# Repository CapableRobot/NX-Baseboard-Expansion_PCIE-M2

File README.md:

# NX Baseboard Expansion : PCIe m2 E-Key

This repository holds the open-source files for the PCIe m2 E-Key add-on to the NX Baseboard.  The [NX Baseboard](https://github.com/antmicro/jetson-nano-baseboard) is also open-source, is designed by Antmicro, and is [sold by Capable Robot Components](https://capablerobot.com/products/nx-baseboard/).

Assembled and tested PCBAs are available for purchase on the [Capable Robot website](https://capablerobot.com/products/nx-baseboard/).

The NX PCIe m.2 E Key PCB provides a standard interface to the NVIDIA NX's PCIe x1 bus, which is exposed on the NX Baseboard via a 10-pin FFC connector. Board specifications:

- m.2 E-Key (PCIe + USB), 2230 size. This is commonly used for WIFI modules like the Intel 8265.
- PCIe x1 interface and 3.3v power are connected to the Host via a 10-pin 0.5mm flex cable.
- USB interface exposed via micro-USB port, allowing USB-specific functionality of the installed card (like Bluetooth) to be used if cabled to the Host. With USB connected, a local 5v to 3.3v regulator can be used in lieu of the 3.3v input on the FFC connector.

Hole spacing on the PCB and location of the flex connector matches that of the NX Baseboard, allowing it to be assembled onto the bottom of the Baseboard.

Any WIFI module that supports m.2 E Key 2230 size can be used with the PCB. We recommend (and stock) the Intel 8265 due to built-in support within NVIDIA Jetpack BSPs.

## License Information

| **Type** | **License** |
| --- | --- |
| Hardware | Copyright Capable Robot Components 2020 <br><br>This source describes Open Hardware and is licensed under the [CERN-OHL-P v2](https://ohwr.org/cern_ohl_p_v2.txt). <br/><br/> You may redistribute and modify this documentation and make products using it under the terms of the [CERN-OHL-P v2](https:/cern.ch/cern-ohl). This documentation is distributed WITHOUT ANY EXPRESS OR IMPLIED WARRANTY, INCLUDING OF MERCHANTABILITY, SATISFACTORY QUALITY AND FITNESS FOR A PARTICULAR PURPOSE. Please see the CERN-OHL-P v2 for applicable conditions |
| Software | NA |
| Documentation | [Creative Commons Attribution-ShareAlike](https://creativecommons.org/licenses/by-sa/4.0/) License |

More detailed information about the CERN License is available in the [license](license) folder and on the [CERN website](https://ohwr.org/project/cernohl/wikis/home).

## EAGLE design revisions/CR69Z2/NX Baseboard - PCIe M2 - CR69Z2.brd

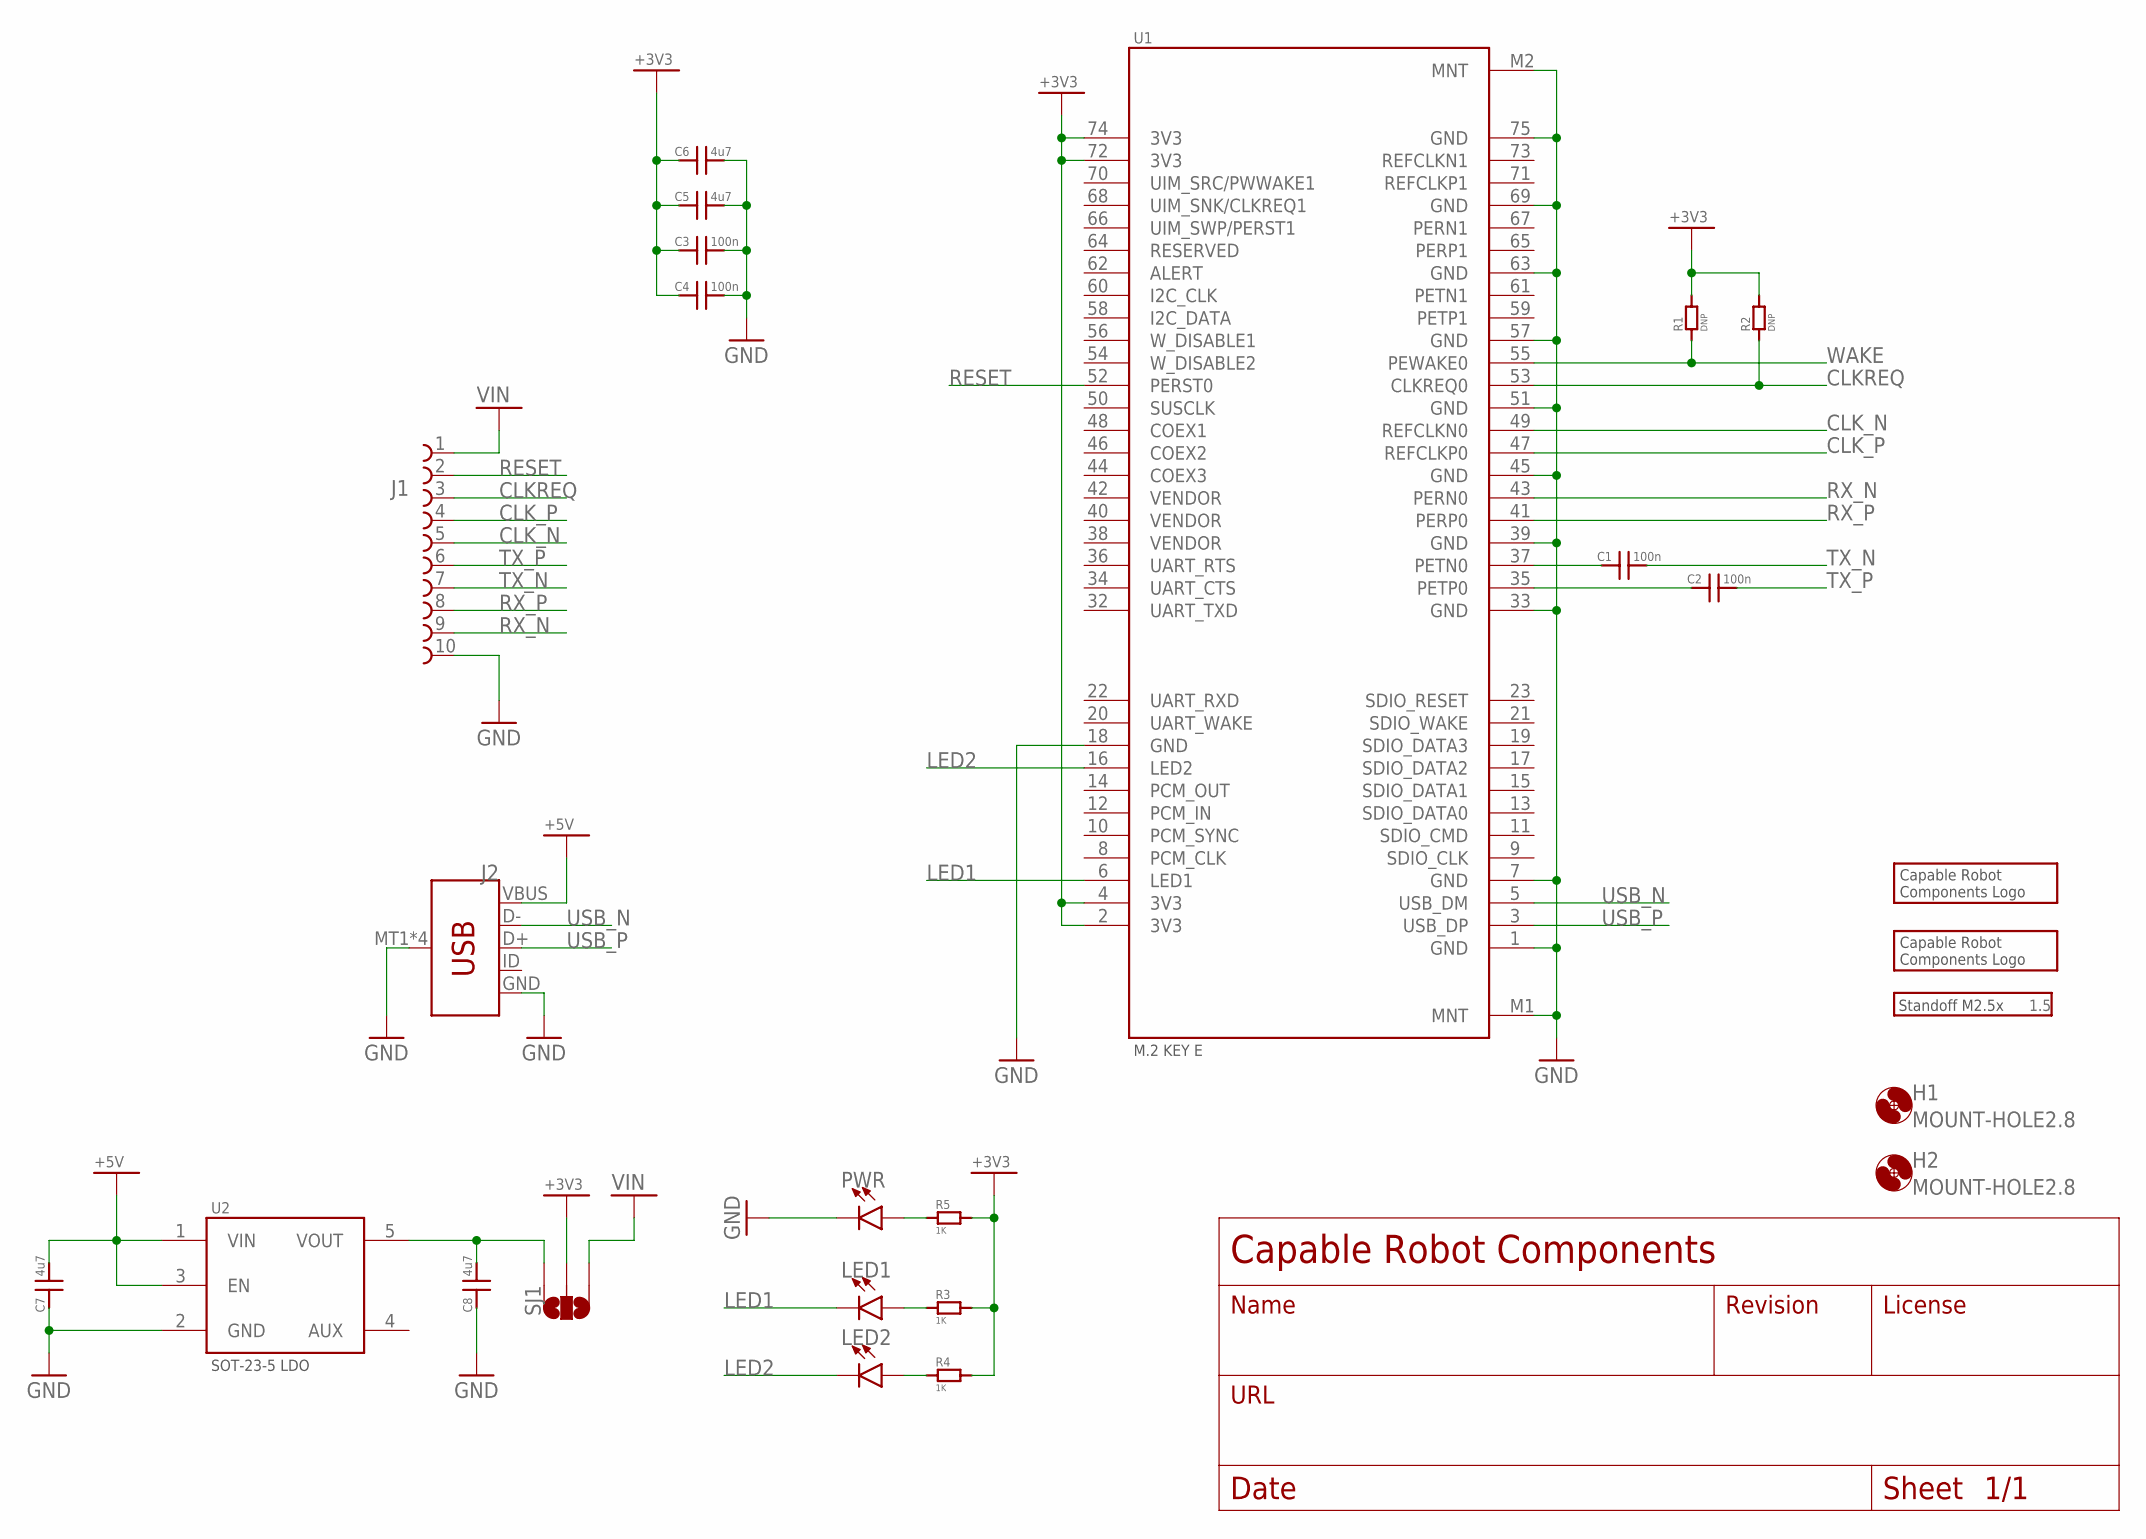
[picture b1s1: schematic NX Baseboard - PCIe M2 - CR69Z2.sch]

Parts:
C1, C2, C3, C4: 100n; 0402
C5, C6, C7, C8: 4u7; 0805
H1, H2: MOUNT-HOLE2.8; 2,8
J1: 68711014522
J2: USB_MICRO-B_SMT; USB-MICROB
LED1, LED2: LED0603; LED-0603
LOGO1: CRC-LOGO10SILK; CRC-LOGO-10-SILK
LOGO2: CRC-LOGO5SILK; CRC-LOGO-5-SILK
M1: 1.5; STANDOFF-M25; MPN 9774015151R
PWR: LED0603; LED-0603
R1, R2: DNP; 0603NOCREAM
R3, R4, R5: 1K; 0603
SJ1: JUMPER-PAD-3-NOYES_SILK; PAD-JUMPER-3-NO_YES_SILK
U1: M2-KEYE; TE-2199119-KEYE; MPN 2199119-4
U2: MIC20XX; SOT25

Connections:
+3V3: C3.1, C4.1, C5.1, C6.1, R1.2, R2.2, R3.2, R4.2, R5.2, SJ1.2, U1.2 (3V3), U1.4 (3V3), U1.72 (3V3), U1.74 (3V3)
+5V: C7.2, J2.VBUS, U2.1 (VIN), U2.3 (EN)
CLKREQ: J1.3, R2.1, U1.53 (CLKREQ0)
CLK_N: J1.5, U1.49 (REFCLKN0)
CLK_P: J1.4, U1.47 (REFCLKP0)
GND: C3.2, C4.2, C5.2, C6.2, C7.1, C8.1, J1.10, J2.GND, J2.MT1 (SHIELD), J2.MT2 (SHIELD), J2.P$1 (SHIELD), J2.P$2 (SHIELD), PWR.C, U1.1 (GND), U1.7 (GND), U1.18 (GND), U1.33 (GND), U1.39 (GND), U1.45 (GND), U1.51 (GND), U1.57 (GND), U1.63 (GND), U1.69 (GND), U1.75 (GND), U1.M1 (MNT), U1.M2 (MNT), U2.2 (GND)
LED1: LED1.C, U1.6 (LED1)
LED2: LED2.C, U1.16 (LED2)
M2_TX_N: C1.1, U1.37 (PETN0)
M2_TX_P: C2.1, U1.35 (PETP0)
unnamed: LED1.A, R3.1
unnamed: LED2.A, R4.1
unnamed: PWR.A, R5.1
RESET: J1.2, U1.52 (PERST0)
RX_N: J1.9, U1.43 (PERN0)
RX_P: J1.8, U1.41 (PERP0)
TX_N: C1.2, J1.7
TX_P: C2.2, J1.6
USB_N: J2.D-, U1.5 (USB_DM)
USB_P: J2.D+, U1.3 (USB_DP)
VIN: J1.1, SJ1.1
VREG: C8.2, SJ1.3, U2.5 (VOUT)
WAKE: R1.1, U1.55 (PEWAKE0)

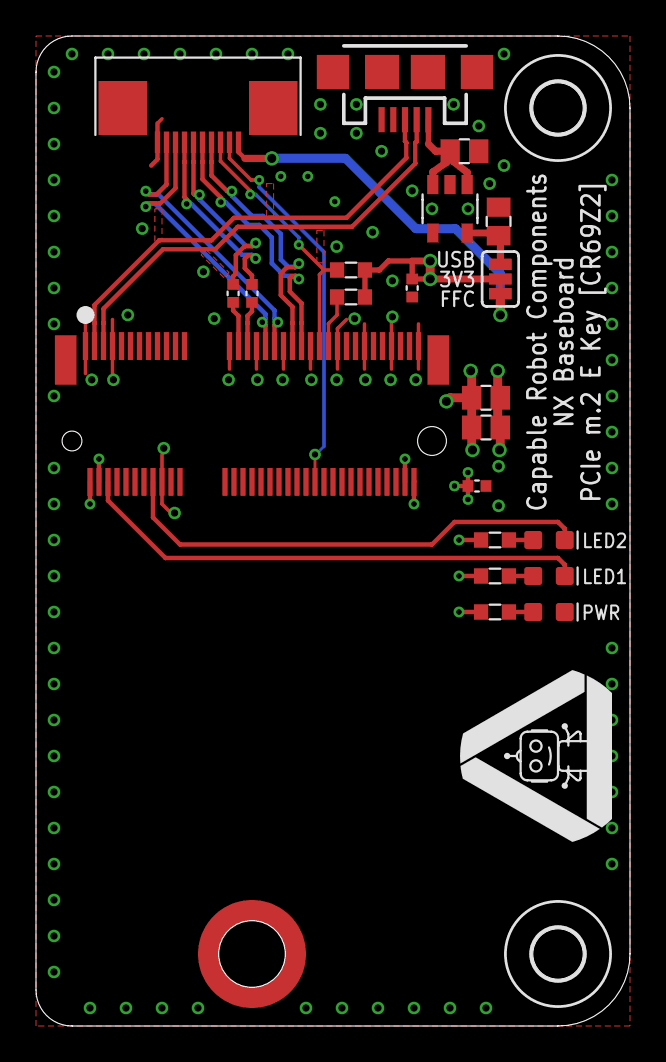
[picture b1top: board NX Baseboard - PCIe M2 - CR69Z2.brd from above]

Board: 4 copper layers, 33.0 x 55.0 mm, 26 parts (1 on the bottom side), 23 nets.

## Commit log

2020-11-22 Add initial release
2020-11-22 Remove obsolete project file
2020-11-22 Trim image edges
2020-12-04 Ignore temporary Eagle files
2020-12-04 Fix alignment hole size on M.2 footprint
2020-12-04 Update exports after hole size change
2020-12-23 Add CERN-OHL-P v2 license

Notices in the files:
parts and their libraries:
Wurth_Elektronik_Electromechanic_FPC_Con: Copyright: Würth Elektronik
SparkFun-LED: Licensing: Creative Commons ShareAlike 4.0 International - https://creativecommons.org/licenses/by-sa/4.0
